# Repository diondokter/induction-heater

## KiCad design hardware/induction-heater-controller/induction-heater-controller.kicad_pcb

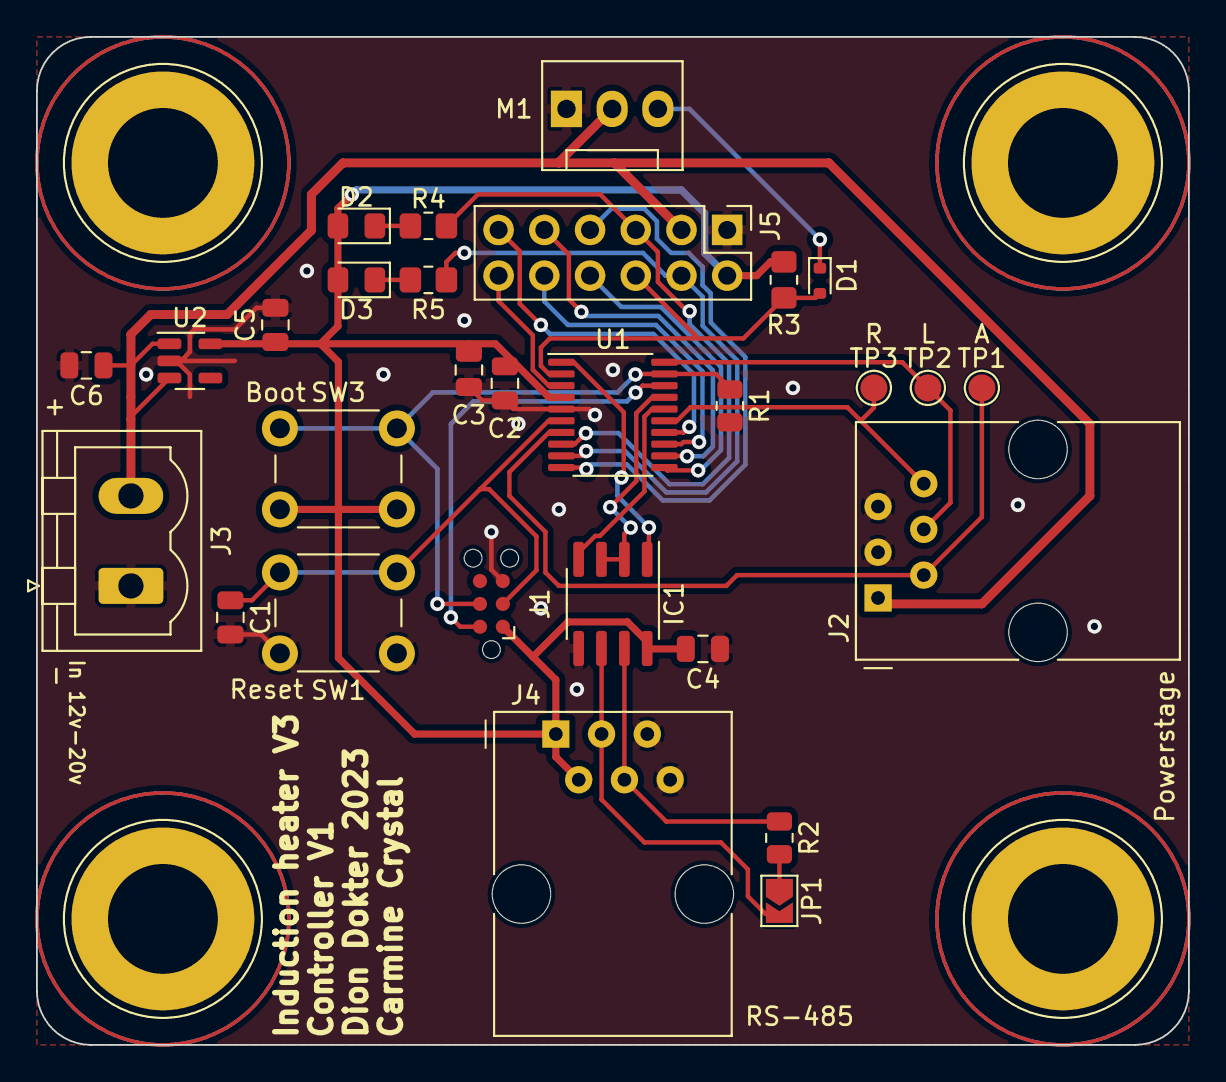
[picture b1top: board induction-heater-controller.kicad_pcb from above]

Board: 2 copper layers, 64.0 x 56.0 mm, 33 parts (0 on the bottom side), 27 nets.

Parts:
C1, C2, C4: 100n; C_0805_2012Metric
C3: 4.7u; C_0805_2012Metric
C5, C6: 1u; C_0805_2012Metric
D1: D; D_SOD-523
D2, D3: LED; LED_0805_2012Metric_Pad1.15x1.40mm_HandSolder
H1, H2, H3, H4: MountingHole; Banana_Jack_1Pin
IC1: THVD1449DR; SOIC-8_3.9x4.9mm_P1.27mm
J1: Conn_ARM_SWD_TagConnect_TC2030-NL; Tag-Connect_TC2030-IDC-NL_2x03_P1.27mm_Vertical
J2, J4: RJ12; RJ12_Amphenol_54601
J3: Screw_Terminal_01x02; PhoenixContact_MSTBVA_2,5_2-G_1x02_P5.00mm_Vertical
J5: Conn_02x06_Top_Bottom; PinHeader_2x06_P2.54mm_Vertical
JP1: SolderJumper_2_Open; SolderJumper-2_P1.3mm_Open_TrianglePad1.0x1.5mm
M1: Fan_3pin; FanPinHeader_1x03_P2.54mm_Vertical
R1: 10k; R_0805_2012Metric
R2: 120; R_0805_2012Metric
R3: 10k; R_0805_2012Metric_Pad1.20x1.40mm_HandSolder
R4: 100; R_0805_2012Metric_Pad1.20x1.40mm_HandSolder
R5: 20; R_0805_2012Metric_Pad1.20x1.40mm_HandSolder
SW1, SW3: SW_Push; SW_PUSH_6mm
TP1, TP2, TP3: TestPoint; TestPoint_Pad_D1.5mm
U1: STM32G030F6Px; TSSOP-20_4.4x6.5mm_P0.65mm
U2: NCP718xSN330; SOT-23-5

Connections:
+3V3: C2.2, C3.2, C4.2, C5.1, D2.2 (A), D3.2 (A), IC1.8 (VCC), J1.1 (VCC), J4.1, J4.2, J5.2, R3.1, SW3.2, U1.4 (VDD), U2.5 (OUT)
ANALOG_L: J2.2, TP1.1, U1.7 (PA0)
DRIVER_L: J2.4, TP2.1, U1.20 (PB3/PB4/PB5/PB6)
DRIVER_R: J2.6, TP3.1, U1.15 (PB0/PB1/PB2/PA8)
FAN_TACHO: D1.2 (A), J5.6, R3.2, U1.2 (PC14/PB9)
GND: C1.2, C2.1, C3.1, C4.1, C5.2, C6.2, IC1.5 (GND), J1.5 (GND), J2.3, J2.5, J3.1, J4.5, J4.6, J5.1, M1.3 (-), R1.2, SW1.2, U1.5 (VSS), U2.2 (GND)
HEADER_7: J5.7, U1.10 (PA3)
HEADER_8: J5.8, U1.11 (PA4)
HEADER_9: J5.9, U1.12 (PA5)
HEADER_10: J5.10, U1.13 (PA6)
HEADER_11: J5.11, U1.14 (PA7)
HEADER_12: J5.12, U1.3 (PC15)
LED_G: J5.4, R5.1, U1.9 (PA2)
LED_R: J5.5, R4.1, U1.8 (PA1)
unnamed: D1.1 (K), M1.1 (Tacho)
unnamed: D2.1 (K), R4.2
unnamed: D3.1 (K), R5.2
unnamed: IC1.6 (A), J4.3, JP1.2 (B)
unnamed: IC1.7 (B), J4.4, R2.1
unnamed: C1.1, J1.3 (~RESET), SW1.1, U1.6 (NRST)
unnamed: JP1.1 (A), R2.2
RS485_DE: IC1.2 (~RE), IC1.3 (DE), U1.17 (PA12/PA10)
RS485_RX: IC1.1 (R), U1.1 (PB7/PB8)
RS485_TX: IC1.4 (D), U1.16 (PA11/PA9)
SWCLK: J1.4 (SWCLK), R1.1, SW3.1, U1.19 (PA14/PA15)
SWDIO: J1.2 (SWDIO), U1.18 (PA13)
VDC: C6.1, J2.1, J3.2, J5.3, M1.2 (+), U2.1 (IN), U2.3 (EN)

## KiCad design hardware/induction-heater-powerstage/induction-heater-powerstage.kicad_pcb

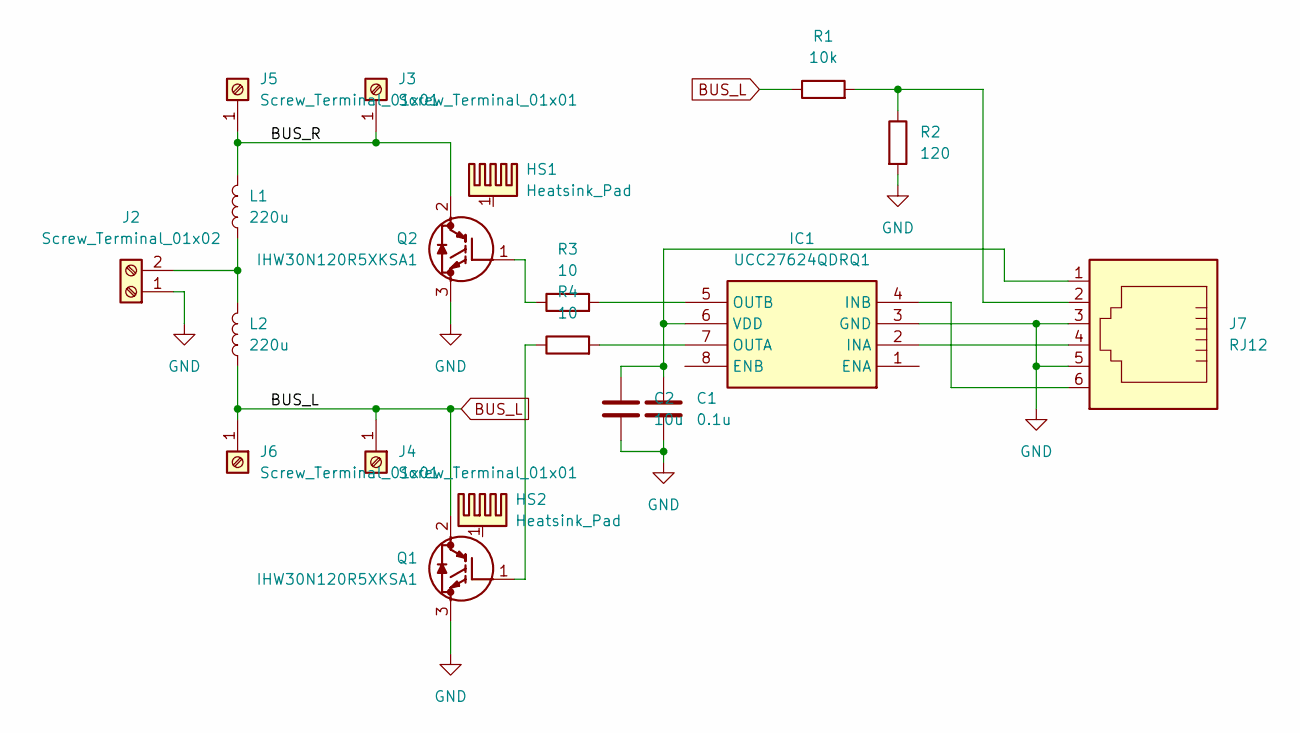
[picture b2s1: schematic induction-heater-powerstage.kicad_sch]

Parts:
C1: 0.1u; C_0805_2012Metric_Pad1.18x1.45mm_HandSolder
C2: 10u; C_0805_2012Metric_Pad1.18x1.45mm_HandSolder
HS1, HS2: Heatsink_Pad; Heatsink_Fischer_SK129-STS_42x25mm_2xDrill2.5mm; MPN 6398BG
IC1: UCC27624QDRQ1; SOIC127P600X175-8N; Mouser Part Number 595-UCC27624QDRQ1
J2: Screw_Terminal_01x02; PhoenixContact_MSTBVA_2,5_2-G_1x02_P5.00mm_Vertical; MPN TB007-508-02BE
J3, J4, J5, J6: Screw_Terminal_01x01; Banana_Jack_1Pin
J7: RJ12; RJ12_Amphenol_54601; MPN 54601-906WPLF
L1, L2: 220u; L_Toroid_Vertical_L31.8mm_W15.9mm_P13.50mm_Bourns_5700; MPN 2300HT-221-V-RC
Q1, Q2: IHW30N120R5XKSA1; TO544P521X1592X2557-3P; Mouser Part Number 726-IHW30N120R5XKSA1
R1: 10k; R_0805_2012Metric_Pad1.20x1.40mm_HandSolder
R2: 120; R_0805_2012Metric_Pad1.20x1.40mm_HandSolder
R3, R4: 10; R_0805_2012Metric_Pad1.20x1.40mm_HandSolder

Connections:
/BUS_R: J3.1, J5.1, L1.2, Q2.2 (C)
BUS_L: J4.1, J6.1, L2.1, Q1.2 (C), R1.1
GND: C1.2, C2.2, IC1.3 (GND), J2.1, J7.3, J7.5, Q1.3 (E), Q2.3 (E), R2.2
unnamed: IC1.2 (INA), J7.4
unnamed: IC1.4 (INB), J7.6
unnamed: IC1.7 (OUTA), R4.2
unnamed: IC1.5 (OUTB), R3.2
unnamed: C1.1, C2.1, IC1.6 (VDD), J7.1
unnamed: J2.2, L1.1, L2.2
unnamed: J7.2, R1.2, R2.1
unnamed: Q1.1 (G), R4.1
unnamed: Q2.1 (G), R3.1

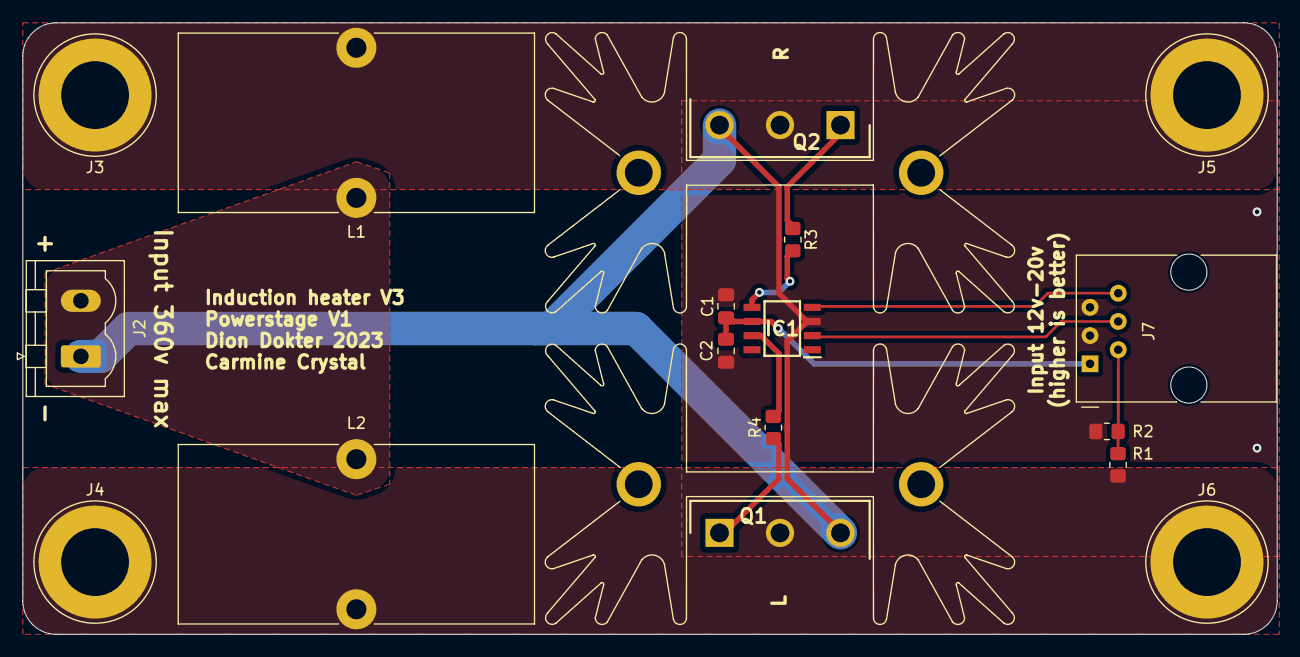
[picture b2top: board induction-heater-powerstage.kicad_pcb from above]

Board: 2 copper layers, 112.8 x 55.0 mm, 19 parts (0 on the bottom side), 12 nets.

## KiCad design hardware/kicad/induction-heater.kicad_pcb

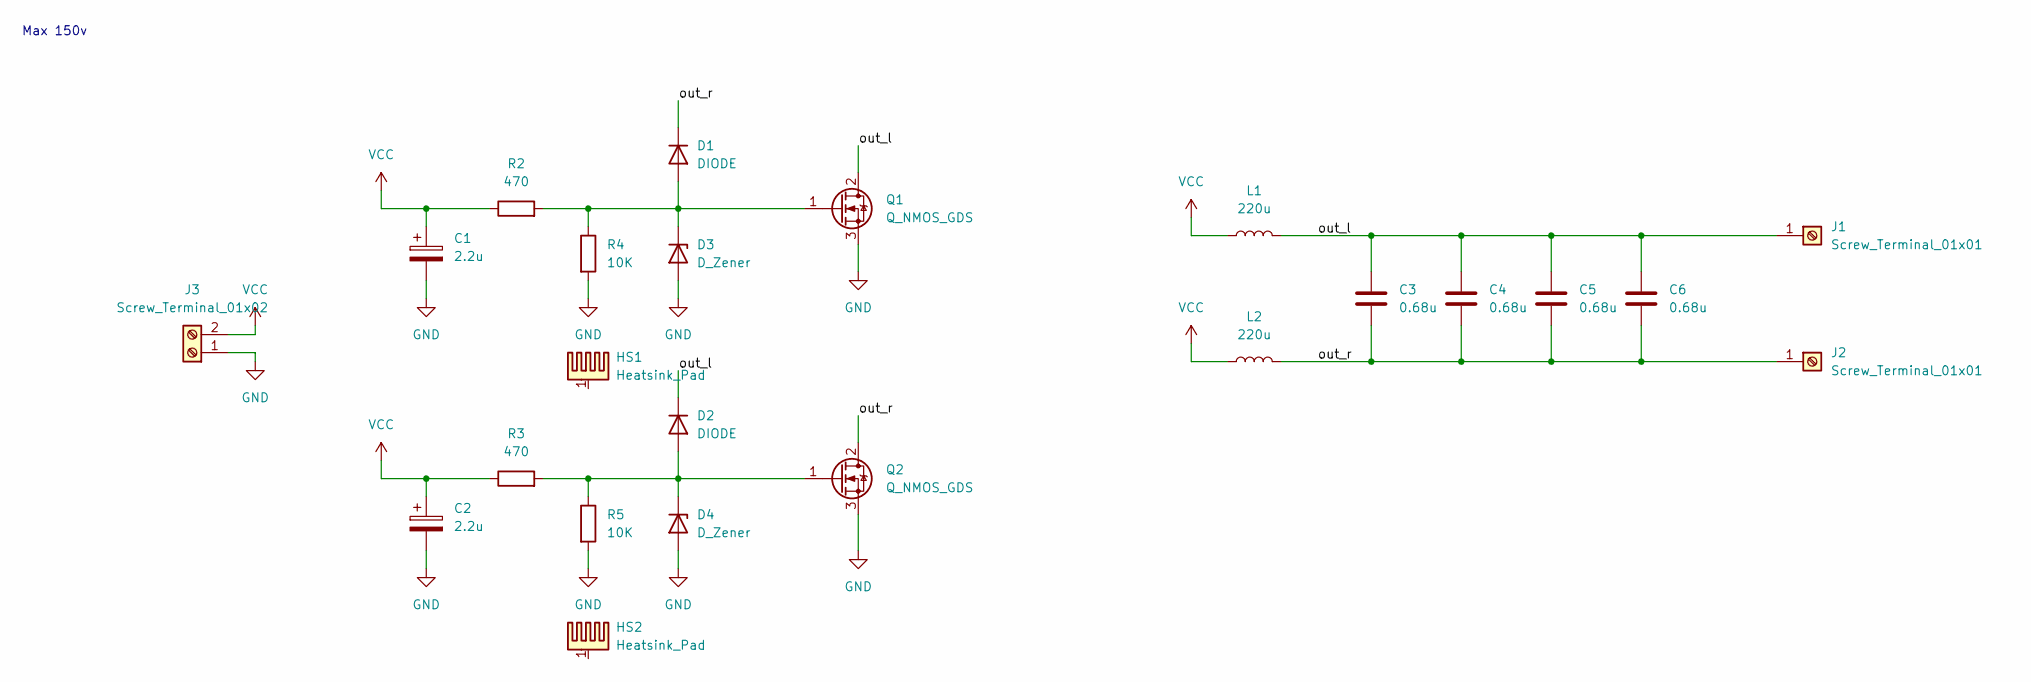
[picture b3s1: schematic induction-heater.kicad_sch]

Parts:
C1, C2: 2.2u; CP_Radial_D6.3mm_P2.50mm; MPN ESL225M250AE3AA
C3, C4, C5, C6: 0.68u; C_Rect_L31.5mm_W15.0mm_P27.50mm_MKS4; MPN MKS4O136806F00KYSD
D1, D2: DIODE; D_DO-41_SOD81_P7.62mm_Horizontal; MPN UF4005-E3/54
D3, D4: D_Zener; D_DO-15_P12.70mm_Horizontal; MPN 1N5927BRLG
HS1, HS2: Heatsink_Pad; Heatsink_Fischer_SK129-STS_42x25mm_2xDrill2.5mm; MPN 6398BG
J1, J2: Screw_Terminal_01x01; Banana_Jack_1Pin
J3: Screw_Terminal_01x02; PhoenixContact_MSTBVA_2,5_2-G_1x02_P5.00mm_Vertical; MPN TB007-508-02BE
L1, L2: 220u; L_Toroid_Vertical_L31.8mm_W15.9mm_P13.50mm_Bourns_5700; MPN 2300HT-221-V-RC
Q1, Q2: Q_NMOS_GDS; TO-220-3_Vertical; MPN NTP067N65S3H
R2, R3: 470; TO-220-2_Vertical; MPN AP851470RJ
R4, R5: 10K; R_Axial_DIN0516_L15.5mm_D5.0mm_P5.08mm_Vertical; MPN ROX3SJ10K

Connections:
/out_l: C3.1, C4.1, C5.1, C6.1, D2.1 (K), J1.1, L1.2, Q1.2 (D)
/out_r: C3.2, C4.2, C5.2, C6.2, D1.1 (K), J2.1, L2.2, Q2.2 (D)
GND: C1.2, C2.2, D3.2 (A), D4.2 (A), J3.1, Q1.3 (S), Q2.3 (S), R4.2, R5.2
unnamed: D1.2 (A), D3.1 (K), Q1.1 (G), R2.2, R4.1
unnamed: D2.2 (A), D4.1 (K), Q2.1 (G), R3.2, R5.1
VCC: C1.1, C2.1, J3.2, L1.1, L2.1, R2.1, R3.1

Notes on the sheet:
Max 150v

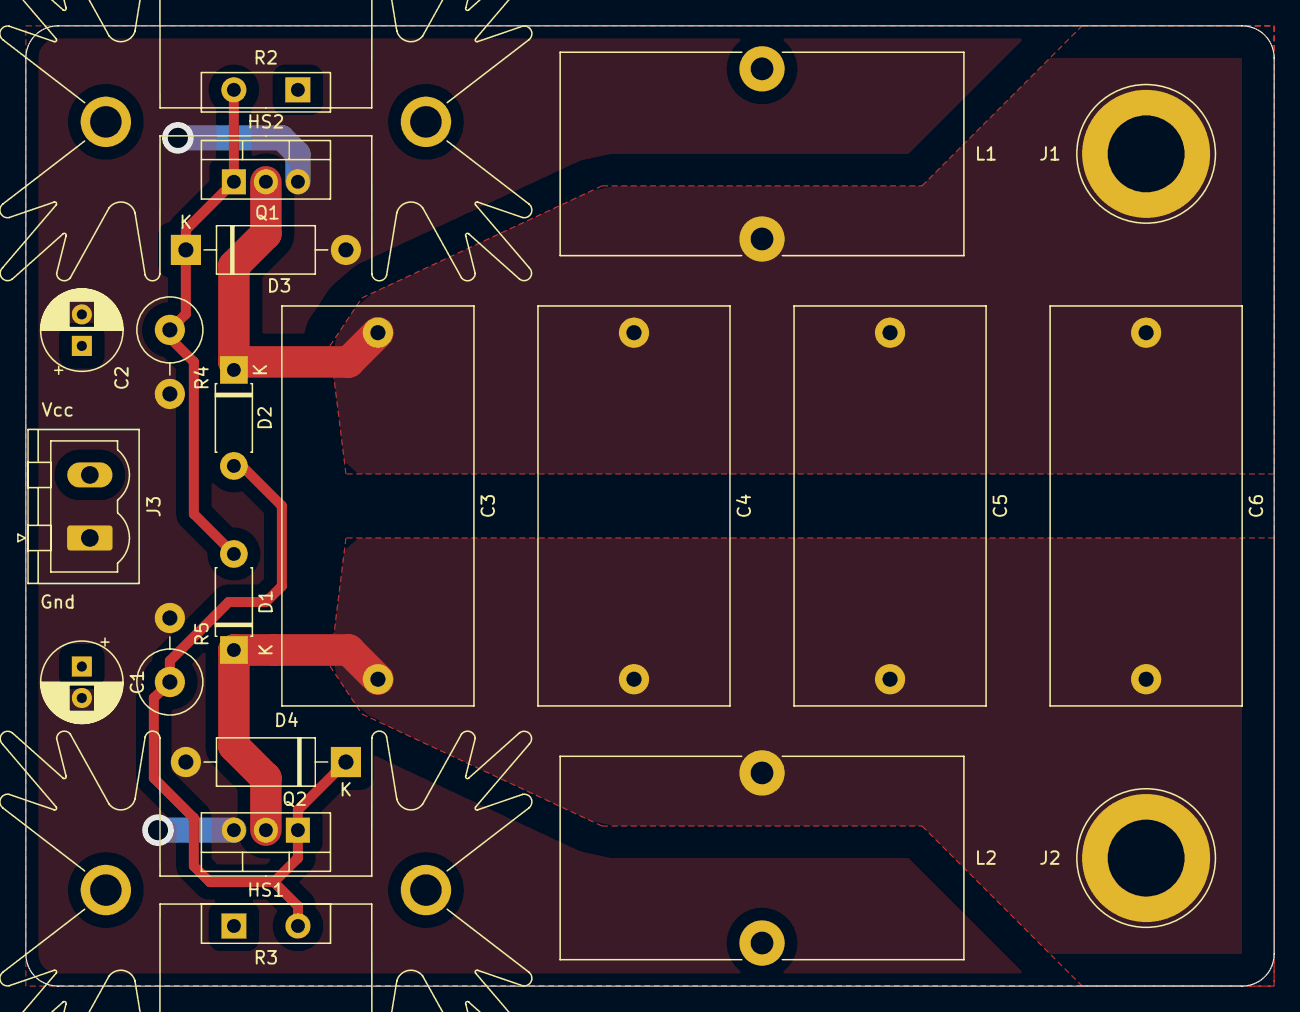
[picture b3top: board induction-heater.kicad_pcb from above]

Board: 2 copper layers, 99.1 x 76.2 mm, 23 parts (0 on the bottom side), 6 nets.

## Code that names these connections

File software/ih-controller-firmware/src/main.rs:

#![no_std]
#![no_main]
#![feature(type_alias_impl_trait)]
#![feature(generic_arg_infer)]

use defmt::unwrap;
use embassy_executor::{InterruptExecutor, SendSpawner, Spawner};
use embassy_stm32::{
    bind_interrupts,
    gpio::{Level, OutputOpenDrain, OutputType, Pull, Speed},
    interrupt::{self, InterruptExt, Priority},
    peripherals::{self, USART1},
    rcc::{AHBPrescaler, APBPrescaler, ClockSrc, PllConfig},
    time::khz,
    timer::{
        simple_pwm::{PwmPin, SimplePwm},
        CountingMode,
    },
    usart::{self, Uart},
};
use {defmt_rtt as _, panic_probe as _};

mod coil_driver;
mod coil_measure;
mod leds;
pub mod modbus;
mod tacho_measure;

bind_interrupts!(struct Irqs {
    USART1 => usart::InterruptHandler<peripherals::USART1>;
});

static EXECUTOR_HIGH: InterruptExecutor = InterruptExecutor::new();

#[cortex_m_rt::interrupt]
unsafe fn RTC_TAMP() {
    EXECUTOR_HIGH.on_interrupt()
}

#[embassy_executor::main]
async fn main(thread_mode_spawner: Spawner) {
    interrupt::RTC_TAMP.set_priority(Priority::P15);
    let interrupt_spawner = EXECUTOR_HIGH.start(interrupt::RTC_TAMP);

    run(thread_mode_spawner, interrupt_spawner).await;
}

async fn run(thread_mode_spawner: Spawner, interrupt_spawner: SendSpawner) {
    let mut stm_config = embassy_stm32::Config::default();
    stm_config.rcc.mux = ClockSrc::PLL(PllConfig::default()); // Make the core run at 64 Mhz
    stm_config.rcc.ahb_pre = AHBPrescaler::DIV1; // We want everything to run at 64 Mhz
    stm_config.rcc.apb_pre = APBPrescaler::DIV1; // Required for the ADC (and we want everything to run at 64 Mhz)
    let p = embassy_stm32::init(stm_config);

    // Remap PA11 to PA9. All other IO's are fine
    embassy_stm32::pac::SYSCFG
        .cfgr1()
        .modify(|w| w.set_pa11_rmp(true));

    let measure_adc = p.ADC1;
    let measure_pin = p.PA0; // ADC_IN0
    let measure_dma = p.DMA1_CH3;

    let led_g = OutputOpenDrain::new(p.PA2, Level::High, Speed::Low, Pull::None);
    let led_r = OutputOpenDrain::new(p.PA1, Level::High, Speed::Low, Pull::None);

    let mut config = usart::Config::default();
    config.baudrate = 921600;
    let rs485 = unwrap!(Uart::new_with_de(
        p.USART1, p.PB7, p.PA9, Irqs, p.PA12, p.DMA1_CH1, p.DMA1_CH2, config,
    ));

    let driver_pwm = SimplePwm::new(
        p.TIM1,
        Some(PwmPin::new_ch1(p.PA8, OutputType::PushPull)),
        Some(PwmPin::new_ch2(p.PB3, OutputType::PushPull)),
        None,
        None,
        khz(40),
        CountingMode::CenterAlignedBothInterrupts,
    );

    let fan_tacho_timer = p.TIM17;
    let fan_tacho_pin = p.PB9; // CH1

    thread_mode_spawner.must_spawn(leds::leds(led_g, led_r));
    interrupt_spawner.must_spawn(modbus::modbus_server(1, rs485));
    interrupt_spawner.must_spawn(coil_driver::coil_driver(driver_pwm));
    thread_mode_spawner.must_spawn(coil_measure::coil_measure(
        measure_adc,
        measure_pin,
        measure_dma,
    ));
    thread_mode_spawner.must_spawn(tacho_measure::tacho_measure(fan_tacho_timer, fan_tacho_pin));
}

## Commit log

2022-10-07 initial
2022-10-07 next
2022-11-04 Components chosen and board layout made
2022-11-10 Compacter board
2022-11-18 Final touches on silkscreen
2022-11-18 Changed mfr to mpn
2022-11-27 Improved the footprints
2022-11-27 Finishing up
2022-11-27 Update gitignore
2022-11-27 Remove backups
2022-11-27 Initial script
2022-11-27 added docs file
2022-11-27 Added jlcpcb script
2022-12-02 Fixed resistor pin assignment on board
2022-12-02 Updated simulation
2023-01-13 V2 done. Also added a new simulation design for a possible v3
2023-07-28 Added new design simulation
2023-07-28 Added gitignore
2023-07-28 Started with the new version
2023-07-29 Fixed the mosfet driver grounds
2023-08-03 Move to IGBTs
2023-08-05 Finished board for controller
2023-08-05 Final components
2023-08-11 Started firmware project
2023-08-13 Built out more of the modbus
2023-08-13 Moved driver to own module and finished it. Added leds task. Started on measure task.
2023-08-14 Gave everything better names
2023-08-14 Set up the full adc config. Hope it's ok!
2023-08-15 Added some math to find the best frequency for the samples
2023-08-16 Improved the sin fitting calcs
2023-08-19 Better fit function
2023-08-19 Refactored ADC code
2023-08-19 Added tachometer code
2023-08-20 Optimize
2023-08-22 Updated deps
2023-08-27 Fixes + start with CLI
2023-08-27 Cleanup
2023-08-29 Added selectable graphs
2023-09-01 Added interrupt executor to firmware. Fixed cli modbus reconnect
2023-09-08 Various fixes
2023-09-10 Modbus refactoring
2023-09-10 Add ADC samples and refine ADC setup
2023-09-10 Faster ADC measure
2023-09-10 Clippy
2023-10-07 Update deps
2023-10-20 Move to simple pwm and slow dutycycle changes
2023-10-20 Add dutycycle control
2023-11-16 Switch polarity
2024-02-13 Remove the playing with dutycycle
2024-03-13 Use modbus value
2024-03-13 Actually enable and disable the pwm
